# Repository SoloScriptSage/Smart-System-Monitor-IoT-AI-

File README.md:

# CortexNode — Smart System Monitor

**CortexNode** is a compact IoT device that monitors PC/server metrics including temperature, fan speed, power consumption, and voltage. It transmits real-time data to a dashboard and optionally integrates AI for predictive maintenance. This project demonstrates PCB design, embedded firmware, and full-stack development in a single package.

---

## Features

* **Real-time monitoring**: Temperature (TMP36), voltage/current (INA219), and system metrics.
* **Display**: Onboard 128×64 OLED shows live readings.
* **Wireless connectivity**: ESP32 Wi-Fi module sends data to cloud or dashboard.
* **AI predictive analysis** *(optional)*: TensorFlow Lite Micro model predicts trends and anomalies.
* **Battery-powered**: 18650 Li-ion with TP4056 charger and 3.3 V buck-boost regulator.
* **Compact PCB design**: Ready for prototyping or custom enclosures.

---

## Hardware Components

| Ref                   | Component                 | Notes                               |
| --------------------- | ------------------------- | ----------------------------------- |
| ESP32-WROOM-32        | Microcontroller           | Wi-Fi + I²C interface               |
| INA219AIDR            | Current/Voltage sensor    | Measures load and power consumption |
| TMP36xS               | Analog temperature sensor | Reads temperature                   |
| OLED 128×64 (SSD1306) | Display                   | I²C interface                       |
| 18650 Li-ion          | Battery                   | 2500–3500 mAh                       |
| TP4056                | Charger/protection        | 1S Li-ion                           |
| Buck-boost module     | 1S → 3.3 V                | Powers ESP32 and peripherals        |

---

## Software Stack

* **Firmware**: Arduino/C++ for ESP32
* **I²C Libraries**: Adafruit_INA219, Adafruit_SSD1306
* **Backend / Dashboard**: Python (FastAPI) or C# Blazor + SignalR
* **Frontend**: React or Blazor WebAssembly
* **Optional AI**: TensorFlow Lite Micro for predictive analytics

---

## Connections

* **ESP32 I²C**: SDA → GPIO21, SCL → GPIO22
* **INA219**: VS+ → 3.3 V, GND → GND, SDA/SCL → ESP32 I²C, VIN+/VIN– → load
* **TMP36**: VCC → 3.3 V, GND → GND, VOUT → GPIO34 (ADC input)
* **OLED**: VCC → 3.3 V, GND → GND, SDA/SCL → ESP32 I²C

---

## Power Supply

* **Battery**: 1 × 18650 Li-ion
* **Charger**: TP4056 module with protection
* **Voltage Regulation**: Buck-boost module outputs stable 3.3 V to ESP32, sensors, and display
* **Decoupling**: 0.1 µF ceramic + 10 µF bulk capacitor near ESP32

---

## Getting Started

1. **Assemble hardware**: Connect ESP32, sensors, OLED, and power circuit as per schematic.
2. **Flash firmware**: Use Arduino IDE or PlatformIO.
3. **Install libraries**: `Adafruit_INA219`, `Adafruit_SSD1306`
4. **Configure Wi-Fi & dashboard**: Update SSID, password, and backend endpoint.
5. **Run dashboard**: Launch React/Blazor frontend to visualize metrics.
6. **Optional**: Deploy TinyML model for predictive monitoring.

---

## Future Improvements

* Add multiple sensor nodes for distributed monitoring
* Integrate cloud services (Azure/AWS) for historical analysis
* Implement low-power deep sleep for longer battery life
* Extend AI models for fan failure and voltage anomaly prediction

---

## License

MIT License — free to use, modify, and distribute.

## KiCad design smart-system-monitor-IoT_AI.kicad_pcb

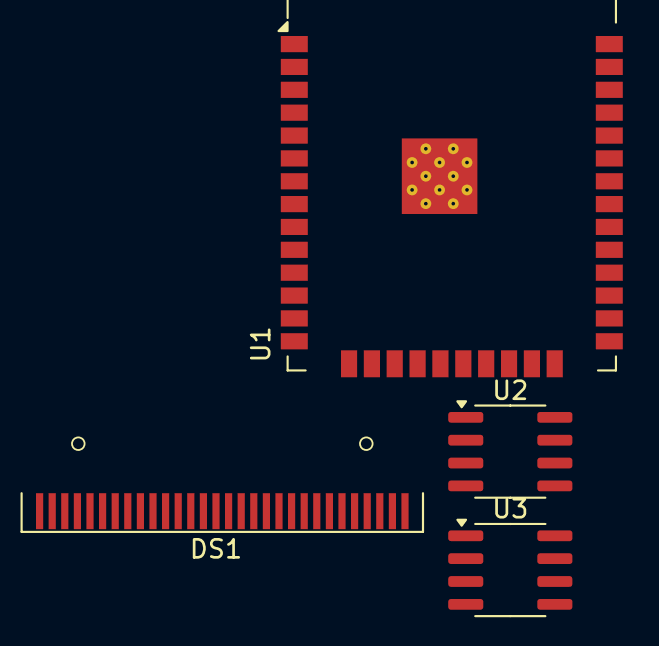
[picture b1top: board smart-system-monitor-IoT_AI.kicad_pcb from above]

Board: 2 copper layers, 4 parts (0 on the bottom side), 5 nets, no tracks yet.

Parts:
DS1: OLED-128O064D
U1: ESP32-WROOM-32
U2: INA219AxD; SOIC-8_3.9x4.9mm_P1.27mm
U3: TMP36xS; SOIC-8_3.9x4.9mm_P1.27mm

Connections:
GND: U1.1 (GND), U1.15 (GND), U1.38 (GND), U1.39 (GND), U2.6 (GND)
unnamed: DS1.1 (GND), DS1.30 (GND)
unnamed: U1.33 (IO21), U2.3 (SDA)
unnamed: U1.36 (IO22), U2.4 (SCL)
unnamed: U1.6 (IO34), U3.1 (V_{OUT})

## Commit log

2025-11-11 Initial commit\
2025-11-11 Assembling
2025-11-11 Folder management
2025-11-11 Add README.md with project details and instructions
    Added detailed project overview, features, hardware components, software stack, connections, power supply information, getting started guide, future improvements, and license details.
2025-11-12 Starting the PCB design
2025-11-13 Finishing up with schematics
